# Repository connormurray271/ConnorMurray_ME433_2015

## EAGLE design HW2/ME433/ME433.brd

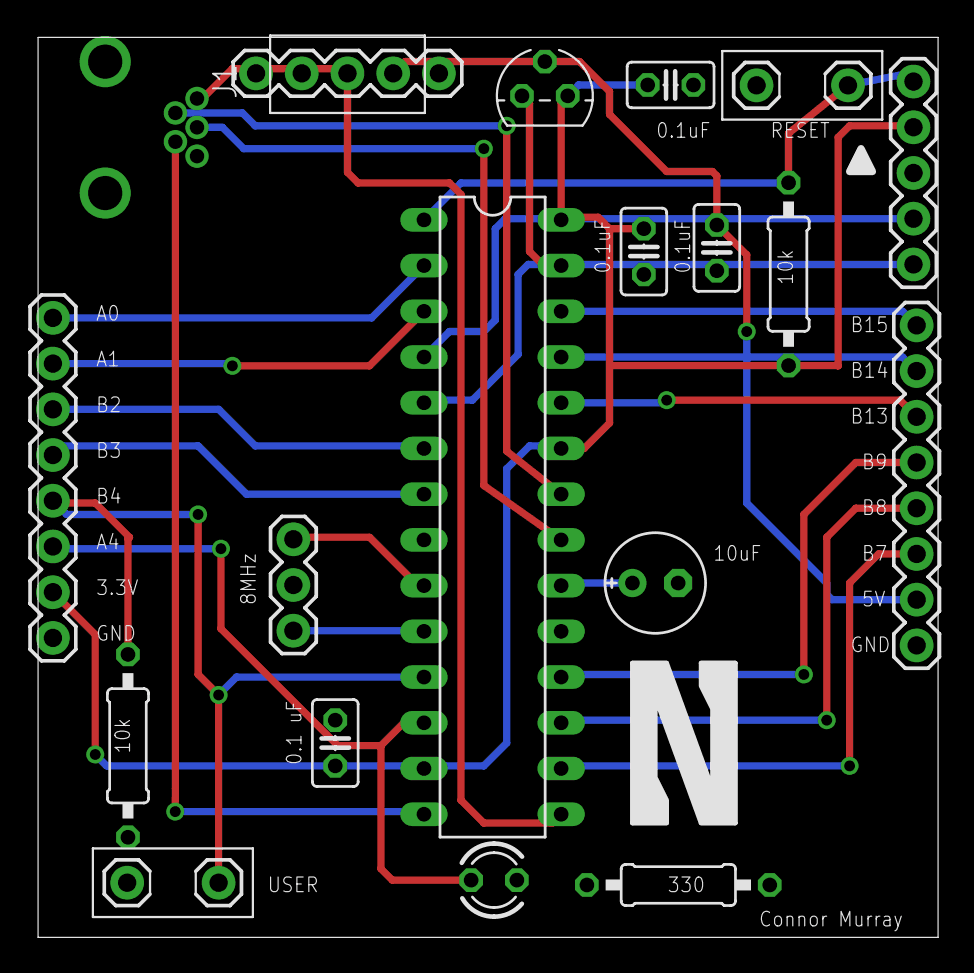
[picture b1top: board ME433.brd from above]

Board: 2 copper layers, 50.0 x 50.0 mm, 19 parts (0 on the bottom side), 26 nets.

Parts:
10UF: E2,5-6E
C1, C2, C4, C5: C025-025X050
CRYSTAL: 1X03
J1: USB-MB-H
J2, J3: 1X08_ROUND
LED1: LED3MM
PB2: PUSHBUTTON
PB(MCLR): PUSHBUTTON
PICKIT: 1X05
R1, R2, R3: 0207/10
U$1: PIC32MX250F128B; DIL28-3
U$4: MCP1702; TO92
U$5: SLIDESWITCH

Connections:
+3V3: C1.1, C2.1, C5.1, J2.2, PICKIT.4, R1.2, U$1.13, U$1.23, U$1.28, U$4.3
+5V: C4.1, J3.7, U$4.2, U$5.4
A0: J2.8, U$1.2
A1: J2.7, U$1.3
A4: J2.3, LED1.A, U$1.12
B2: J2.6, U$1.6
B3: J2.5, U$1.7
B4: J2.4, PB2.3, R2.2, U$1.11
B7: J3.6, U$1.16
B8: J3.5, U$1.17
B9: J3.4, U$1.18
B13: J3.3, U$1.24
B14: J3.2, U$1.25
B15: J3.1, U$1.26
D+: J1.D+, U$1.21
D-: J1.D-, U$1.22
GND: 10UF.-, C1.2, C2.2, C4.2, C5.2, CRYSTAL.2, J1.GND, J2.1, PB2.1, PB(MCLR).3, PICKIT.3, R2.1, R3.1, U$1.8, U$1.19, U$1.27, U$4.1
MCLR: PB(MCLR).1, PICKIT.5, R1.1, U$1.1
unnamed: CRYSTAL.3, U$1.9
unnamed: 10UF.+, U$1.20
unnamed: LED1.K, R3.2
unnamed: CRYSTAL.1, U$1.10
PGC: PICKIT.1, U$1.5
PGD: PICKIT.2, U$1.4
USBID: J1.ID, U$1.14
VBUS: J1.VBUS, U$1.15, U$5.3

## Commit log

2016-03-31 My first commit
2016-03-31 2nd commit
2016-04-05 Initial file creation
2016-04-05 Unable to get PIC to work
2016-04-05 Photos
2016-04-05 Pragmas are correct, but does not build still
2016-04-05 Main added, build good, still comm problems
2016-04-07 Timing works
2016-04-07 Library started
2016-04-07 PIC32 added to library
2016-04-12 Library complete
2016-04-12 Schematic complete
2016-04-14 board finished
2016-04-14 Ready to be checked before order
2016-04-21 pins initialized
2016-04-21 spi initialized
2016-04-21 spi code written but not tested
2016-04-21 starting setVoltage function
2016-04-22 setVoltage written
2016-04-22 trouble with including header files
2016-04-24 i2c initialized, spi still not debugged
2016-04-24 expander init
2016-04-24 i2c written
2016-04-24 i2c written but not working
2016-04-24 fixed out pin, clock still not oscillating
2016-04-30 spi still not working
2016-04-30 sck1 not working
2016-04-30 i2c complete
2016-05-01 initIMU code written
2016-05-02 whomami works
2016-05-02 50% pwm set
2016-05-05 imu complete
2016-05-05 spi complete
2016-05-10 can't communicate with lcd
2016-05-10 Android Hello World complete
2016-05-10 slider complete
2016-05-11 drawCharacter works
2016-05-11 writing to screen complete
2016-05-11 emu lcd code written
2016-05-12 imu prints to lcd
2016-05-15 hw5 complete
2016-05-24 camera app started
2016-05-24 added slider to change row
2016-05-24 add physical color slider
2016-05-29 imu and lcd work with pcb
2016-05-29 added color slider
2016-05-29 COM for 3 lines
2016-05-29 added angle calculator
2016-05-29 tracks brown line
2016-06-01 pic not showing on phone
2016-06-06 HelloWorld and Camera work with 5.1
2016-06-06 does not read PIC
2016-06-06 pic communicates with phone
2016-06-07 cdc complete
2016-06-07 slider bar added
2016-06-07 pic doesn't send slider back
2016-06-07 comm with pic works
2016-06-07 led slider control
2016-06-07 app not opening
2016-06-07 Android CDC complete
2016-06-07 car drives
2016-06-09 finishing commit
